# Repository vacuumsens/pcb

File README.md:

# PCB Schematic Projects

KiCad PCB design projects for VacuumSens.

## Project Structure

```
SchematicProjects/
├── libs/                    # Centralized component libraries
│   ├── easyeda2kicad.kicad_sym
│   ├── easyeda2kicad.pretty/
│   └── easyeda2kicad.3dshapes/
├── charging-circuit/V1/     # Charging circuit project
├── RS232-converter/V1/      # RS232 converter project
└── ...
```

## Importing Components from EasyEDA/LCSC

There are two methods to import components:

---

### Method 1: Command Line (easyeda2kicad)

Best for batch imports or when you know the LCSC part number.

#### Prerequisites

Install the `easyeda2kicad` Python tool:

```bash
pip install easyeda2kicad
```

#### Import a Component

Use the alias (already configured in `.zshrc`):

```bash
easyeda2kicad-import <LCSC_ID>
```

**Example:**
```bash
easyeda2kicad-import C49018
```

This downloads the symbol, footprint, and 3D model to the centralized `libs/` folder.

#### Manual Import (without alias)

```bash
easyeda2kicad --full --overwrite --output /Users/andrewyanez/Documents/KiCad/7.0/symbols/SchematicProjects/libs --lcsc_id C49018
```

---

### Method 2: KiCad Plugin (EasyEDA/LCSC Plugin)

Best for browsing and importing directly within KiCad.

#### Installation

1. In KiCad, go to **Plugin and Content Manager**
2. Search for "EasyEDA" or "LCSC"
3. Install the plugin

#### Usage

1. Open your KiCad project
2. Go to **Tools → EasyEDA Library** (or similar menu item)
3. Search for a component by name or LCSC part number
4. Click **Import** - the plugin will create:
   - `LCSC/EasyEDA.kicad_sym` (symbols)
   - `LCSC/EasyEDA.pretty/` (footprints)
   - `LCSC/EasyEDA.3dshapes/` (3D models)

**Note:** The plugin saves files locally in your project folder under `LCSC/`. This is project-specific, not centralized.

---

### After Importing (Both Methods)

1. Open your KiCad project
2. The library should be available in the schematic/PCB editor
3. Add the new symbol/footprint to your design
4. Commit changes to git:
   ```bash
   git add -A && git commit -m "Add component CXXXXX"
   git push
   ```

---

### Which Method to Use?

| Method | Pros | Cons |
|--------|------|------|
| **easyeda2kicad** (CLI) | Centralized in `libs/`, shared across projects | Requires terminal |
| **KiCad Plugin** | Visual browsing, integrated in KiCad | Project-local, can create duplicates |

**Recommendation:** Use the CLI for components you'll reuse. Use the plugin for quick project-specific imports.

## Library Configuration

Projects reference the centralized library using relative paths:

**sym-lib-table:**
```
(lib (name "easyeda2kicad")(type "KiCad")(uri "${KIPRJMOD}/../../libs/easyeda2kicad.kicad_sym"))
```

**fp-lib-table:**
```
(lib (name "easyeda2kicad")(type "KiCad")(uri "${KIPRJMOD}/../../libs/easyeda2kicad.pretty"))
```

## Finding LCSC Part Numbers

1. Go to [LCSC.com](https://www.lcsc.com) or [JLCPCB Parts](https://jlcpcb.com/parts)
2. Search for your component
3. The LCSC part number starts with "C" (e.g., C49018)

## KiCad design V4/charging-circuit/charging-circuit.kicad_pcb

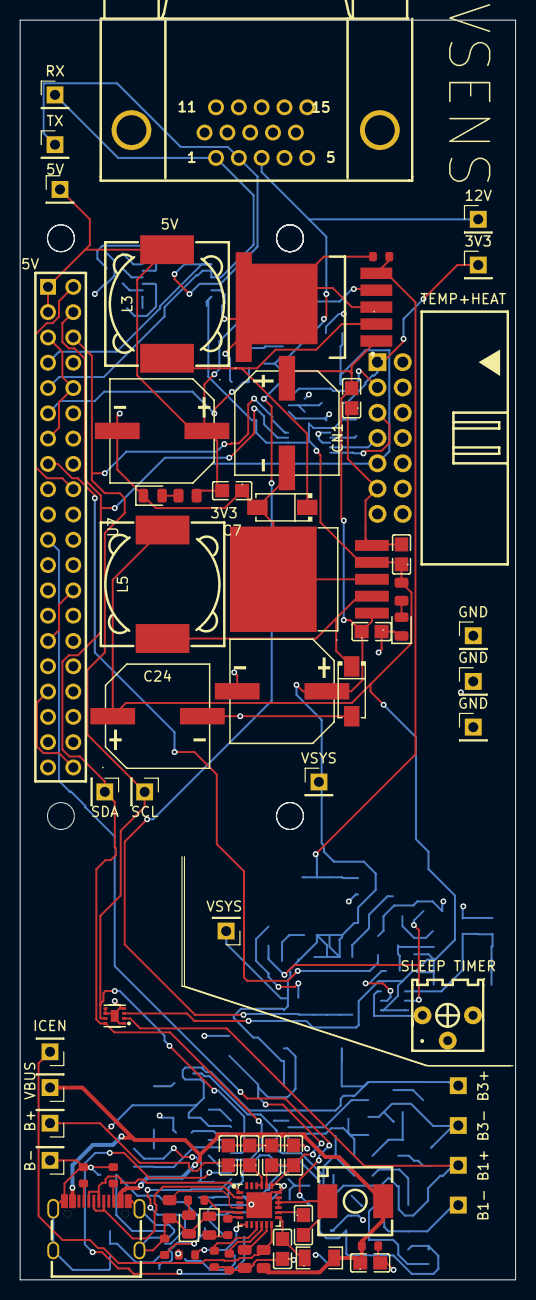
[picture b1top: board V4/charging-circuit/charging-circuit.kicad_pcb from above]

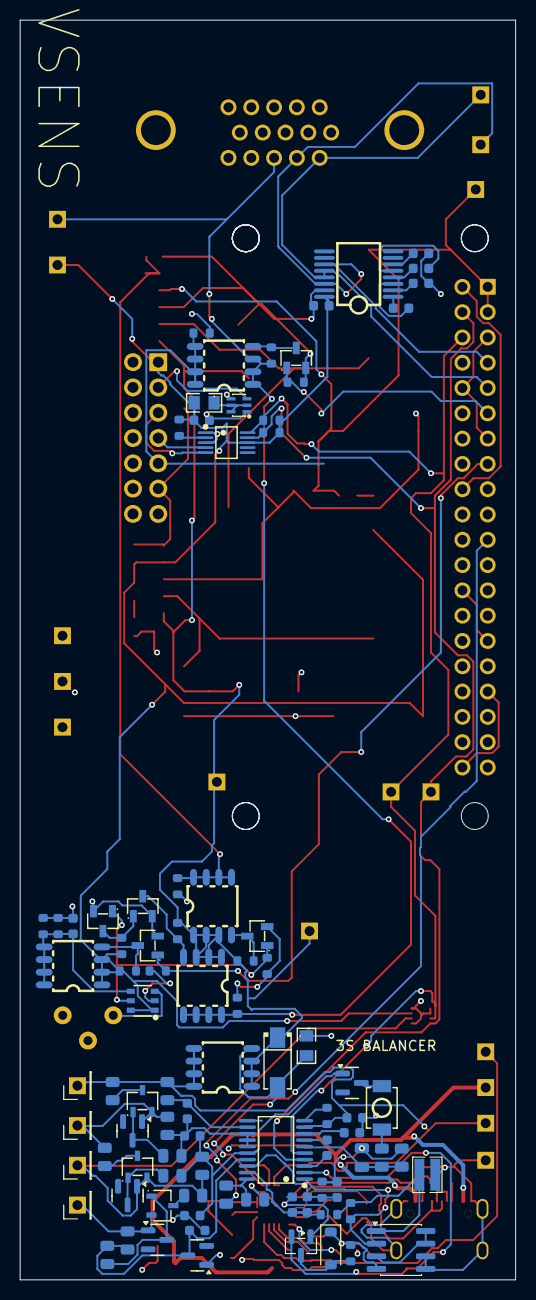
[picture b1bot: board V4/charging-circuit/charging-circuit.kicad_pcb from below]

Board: 4 copper layers, 49.8 x 126.5 mm, 153 parts (88 on the bottom side), 87 nets.

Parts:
3V3: 3V3; PinHeader_1x01_P2.54mm_Vertical
12V: 12VOUT; PinHeader_1x01_P2.54mm_Vertical
C2, C3, C6, C7, C19: 100nf; C0805
C4, C5: 22uf; C0805
C8, C10, C11, C12: 10uf; C0805
C13, C14, C15, C16, C18, C22, C29, C33, C35, C36, C65: 100nF; C_0603
C21: 330uf; CAP-SMD_BD10.0-L10.3-W10.3-FD
C23, C24, C25: 470uf; CAP-SMD_BD10.0-L10.3-W10.3-LS11.0-FD
C27: 100nF; C_0805
C38, C39: 1uF; C_0603
C40: 4.7uF; C_0603
CN1: DC3-2.54-14PAL; IDC-TH_14P-P2.54_ZHOURI_DC3-2.54-14PAL
C_sense7, C_sense8, C_sense9: 100nF; C_0603
D1, D2, D5: SS54_C22452; SMA_L4.4-W2.8-LS5.4-R-RD
D3, D6, D7, D13: BZX84C5V6; D_SOT-23
D8: Red; D_0805
D9, D10, D12: Green; D_0805
D11: 1N4148W; D_SOD-123
D14: BZX84C3V3; D_SOT-23
DSub2: DS1038-15FBNSIA74-0CC; DSUB-TH_DS1038-15FBNSIA74-0CC
GND: GND; PinHeader_1x01_P2.54mm_Vertical
GND#2, GND#3: GND; PinHeader_1x01_P2.54mm_Vertical
L1: SPM6530T-2R2M; IND-SMD_L7.1-W6.5-P5.60
L3, L5: SMDRI127-330MT; IND-SMD_L12.3-W12.3
Q1, Q2, Q3: DMN2004K-7; SOT-23-3_L3.0-W1.7-P0.95-LS2.9-BR
Q5: AO4892; SOIC-8_3.9x4.9mm_P1.27mm
Q11: BSS84; SOT-23
Q14, Q21, Q24, Q25, Q26: 2N7002; SOT-23-3_L2.9-W1.3-P1.90-LS2.4-BR
Q17, Q18, Q22, Q27, Q28: CJQ4435; SOP-8_L5.0-W4.0-P1.27-LS6.2-BL
Q23: currentmirror; SOT-363-6_L2.2-W1.3-P0.65-LS2.1-BL
R1: 0805W8F2553T5E; R0805
R2, R3: 4.7kΩ; R_0805
R4: 0.5ohm; R1206
R5: 100k; R0805
R6: 3362P-1-204; RES-ADJ-TH_3P-L7.1-W6.9-P2.50-L_3362P
R8, R13, R20: 33Ω; R_0805
R9, R10, R21, R22, R53: 1kΩ; R_0805
R11, R16, R24, R25, R26: 10kΩ; R_0805
R12: 62kΩ; R_0805
R14: 1MΩ; R_0805
R15, R52, R54: 1MΩ; R_0603
R18, R19: 51kΩ; R_0805
R31, R32, R33, R40, R44, R45: 5.1kΩ; R_0603
R37, R38, R39, R41, R43, R47, R50: 10kΩ; R_0603
R46, R48, R49, R51: 100kΩ; R_0603
RPROG8, RPROG9, RPROG10, RPROG11, RPROG12, RPROG13, RPROG14, RPROG15: 1kΩ; R_0603
RX: RX; PinHeader_1x01_P2.54mm_Vertical
R_sense5, R_sense6, R_sense7: 100Ω; R_0603
Rsense3: LTR18EZPFSR015; R0612
SW3: TS-1088R-02026; SW-SMD_L3.9-W3.0-P4.45
TP2, TP3, TP4, TP5, TP9: TestPoint; PinHeader_1x01_P2.54mm_Vertical
TP6: BAT-; PinHeader_1x01_P2.54mm_Vertical
TP7: Bat+; PinHeader_1x01_P2.54mm_Vertical
TP8: VBUS; PinHeader_1x01_P2.54mm_Vertical
TP10: VSYS; PinHeader_1x01_P2.54mm_Vertical
TP15: SDA; PinHeader_1x01_P2.54mm_Vertical
TP16: SCL; PinHeader_1x01_P2.54mm_Vertical
TP21: 5V; PinHeader_1x01_P2.54mm_Vertical
TX: TX; PinHeader_1x01_P2.54mm_Vertical
U1: IP2326; VQFN-24_L4.0-W4.0-P0.50-BL-EP2.5
U2: MAX17048G+T10; TDFN-8_L2.0-W2.0-P0.50-BL-EP1.2
U3: BQ7692003PWR; TSSOP-20_L6.5-W4.4-P0.65-LS6.4-BL
U4: LM2596SX-3.3; TO-263-5_L10.2-W8.6-P1.70-LS14.4-TL
U6: LM2596SX-5.0/NOPB; TO-263-5_L10.2-W8.9-P1.70-TL
U7: 2.54-2*20; HDR-TH_40P-P2.54-V-F-R2-C20-S2.54
U10: MAX3232CDBR; SSOP-16_L6.2-W5.3-P0.65-LS7.8-BL
U12: ADS1115IDGSR; MSOP-10_L3.0-W3.0-P0.50-LS5.0-BL
U19: TPL5110DDCT; TSOT-23-6_L2.9-W1.6-P0.95-LS2.8-BR
USBC1: TYPE-C-31-M-12; USB-C_SMD-TYPE-C-31-M-12_1
VSYS: VSYS2; PinHeader_1x01_P2.54mm_Vertical

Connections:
/3S Balancer/B1-: D7.1, Q3.2 (S), R53.1, TP2.1 (1_1)
/3S Balancer/B3-: D3.1, Q1.2 (S), R10.1, R20.1, TP4.1 (1_1)
/3S Balancer/CHG: Q11.2 (S), U3.2 (CHG)
/3S Balancer/DSG: Q5.2 (G1), R15.1, U3.1 (DSG)
/3S Balancer/PROTECT-: Q5.1 (S1), R15.2, R_sense5.2, Rsense3.1
/3S Balancer/SRN: C_sense7.2, C_sense8.1, R_sense5.1, U3.19 (SRN)
/3S Balancer/SRP: C_sense8.2, C_sense9.1, R_sense6.1, U3.18 (SRP)
/3S Balancer/TS1: C27.1, R25.1, R26.2, U3.6 (TS1)
/3S Balancer/VC0: C18.2, D14.3, R24.2, R53.2, U3.17 (VC0)
/3S Balancer/VC1: C15.2, C16.1, D13.1, R16.2, R21.2, U3.16 (VC1)
/3S Balancer/VC3: C14.2, C15.1, R10.2, R11.2, U3.13 (VC4), U3.14 (VC3), U3.15 (VC2)
/3S Balancer/VC5: C14.1, R9.2, U3.12 (VC5)
/3S IC/BAT+: C8.1, C10.1, C38.1, Q18.5 (D), Q18.6 (D), Q18.7 (D), Q18.8 (D), R8.1, R9.1, R_sense7.1, TP5.1 (1_1), TP7.1 (1_1), U1.21 (VOUT), U1.22 (VOUT), U3.9 (REGSRC)
/3S IC/DN: U1.1 (DM), USBC1.A7 (DN1), USBC1.B7 (DN2)
/3S IC/DP: U1.2 (DP), USBC1.A6 (DP1), USBC1.B6 (DP2)
/3S IC/ICEN: R19.2, TP9.1 (1_1), U1.12 (EN)
/3S IC/ICVBUS: C12.1, L1.2, R4.2, R19.1, R33.2, TP8.1 (1_1), USBC1.A4B9 (VBUS), USBC1.B4A9 (VBUS)
/5V: C7.2, C21.1, L3.2, R2.1, TP21.1 (1_1), U6.4 (FB), U7.1, U7.3
/DSUB+RS232/DSUB3.3V: 3V3.1 (1_1), C13.1, C19.1, C24.1, C33.1, CN1.1, L5.2, Q22.1 (S), Q22.2 (S), Q22.3 (S), R1.2, R3.1, R40.1, R43.2, R44.1, R45.1, R46.1, U2.3 (VDD), U4.4 (FB), U10.16 (VCC), U12.8 (VDD), U19.1 (VDD), U19.6 (EN/ONE_SHOT)
/DSUB+RS232/DSUB12V: 12V.1 (1_1), DSub2.3, Q17.1 (S), Q17.2 (S), Q17.3 (S), Q28.5 (D), Q28.6 (D), Q28.7 (D), Q28.8 (D), R39.2, R49.2
/FUELGAUGE/FUELBAT: D6.1, Q2.2 (S), R13.1, R21.1, TP3.1 (1_1), U2.2 (CELL)
/GND: C3.2, C4.1, C5.1, C6.1, C7.1, C8.2, C10.2, C11.1, C12.2, C13.2, C16.2, C18.1, C19.2, C21.2, C23.2, C24.2, C25.2, C27.2, C29.2, C33.2, C35.2, C38.2, C40.2, C65.2, CN1.11, C_sense7.1, C_sense9.2, D2.1 (A), D5.1 (A), D8.1, D9.1, D10.1, D12.1, D14.1, DSub2.4, GND.1 (1_1), GND#2.1 (1_1), GND#3.1 (1_1), Q5.5 (D2), Q5.6 (D2), Q11.1 (G), Q14.2 (S), Q21.2 (S), Q23.1 (E), Q23.4 (E), Q24.2 (S), Q25.2 (S), Q26.2 (S), R5.1, R6.2, R12.1, R14.2, R18.1, R25.2, R31.1, R32.1, R33.1, R37.2, R38.2, R41.1, R49.1, R50.2, R51.2, R54.2, RPROG8.2, RPROG9.2, RPROG10.2, RPROG11.2, RPROG14.2, RPROG15.2, R_sense6.2, Rsense3.2, TP6.1 (1_1), U1.18 (PGND), U1.25 (EP), U2.1 (CTG), U2.4 (GND), U2.5 (~ALRT), U2.6 (QSTRT), U2.9 (EP), U4.3 (GND), U4.5 (~ON/OFF), U4.6 (GND), U6.3 (GND), U6.6 (GND), U7.5, U7.10, U7.13, U7.19, U7.26, U7.29, U7.33, U7.40, U10.15 (GND), U12.1 (ADDR), U12.3 (GND), U19.2 (GND), USBC1.1 (EH), USBC1.2 (EH), USBC1.3 (EH), USBC1.4 (EH), USBC1.A1B12 (GND), USBC1.B1A12 (GND)
/GPIO2/SDA1: R44.2, TP15.1 (1_1), U2.8 (SDA), U3.4 (SDA), U7.4, U12.9 (SDA)
/GPIO3/SCL1: R45.2, TP16.1 (1_1), U2.7 (SCL), U3.5 (SCL), U7.6, U12.10 (SCL)
/GPIO14/TXD0: DSub2.2, TX.1 (1_1), U7.7, U10.11 (DIN1), U10.14 (DOUT1)
/GPIO15/RXD0: DSub2.1, RX.1 (1_1), U7.9, U10.12 (ROUT1), U10.13 (RIN1)
/GPIO18/PCM.CLK: Q14.1 (G), R50.1, U7.11
/GPIO23: Q21.1 (G), R41.2, U7.15
/GPIO25: R22.1, U7.21
/LM2596 3V3 BUCK/LM2596_VIN: C3.1, C6.2, C23.1, C25.1, D1.2 (K), Q18.1 (S), Q18.2 (S), Q18.3 (S), Q27.1 (S), Q27.2 (S), Q27.3 (S), Q28.1 (S), Q28.2 (S), Q28.3 (S), R47.2, R48.2, TP10.1 (1_1), U4.1 (VIN), U6.1 (VIN), VSYS.1 (1_1)
/LM2596 3V3 BUCK/SW: D5.2 (K), L5.1, U4.2 (OUT)
/LM2596 5V Buck/SW: D2.2 (K), L3.1, U6.2 (OUTPUT)
/Load Sharing/VSYS: C4.2, C5.2, D1.1 (A), Q18.4 (G), R5.2, U1.19 (VSYS), U1.20 (VSYS)
/SLEEPMOSFET/5EN: Q27.5 (D), Q27.6 (D), Q27.7 (D), Q27.8 (D), R51.1, RPROG10.1, U6.5 (~ON/OFF)
/SLEEPMOSFET/SLPDRV: Q24.1 (G), Q25.1 (G), R38.1, U19.5 (DRV)
/SLEEPMOSFET/SLPSIG: C65.1, Q22.5 (D), Q22.6 (D), Q22.7 (D), Q22.8 (D), R37.1, RPROG9.1, U19.4 (DONE)
/TEMP+HEATER/A0: CN1.7, U12.4 (AIN0)
/TEMP+HEATER/A1: CN1.5, U12.5 (AIN1)
/TEMP+HEATER/DIODEI-: CN1.3, Q23.3 (C)
/TEMP+HEATER/HEATER+: CN1.9, Q17.5 (D), Q17.6 (D), Q17.7 (D), Q17.8 (D), RPROG8.1
/TEMP+HEATER/base: Q23.2 (B), Q23.5 (B), Q23.6 (C), R1.1
/raspi3.3V: U7.2, U7.18
unnamed: C2.2, L1.1, U1.15 (LX), U1.16 (LX), U1.17 (LX)
unnamed: D8.2, RPROG13.2
unnamed: D9.2, RPROG12.2
unnamed: D10.2, R2.2
unnamed: D11.2 (A), Q11.3 (D), R52.1
unnamed: D11.1 (K), Q5.4 (G2), R52.2, R54.1
unnamed: D12.2, R3.2
unnamed: D13.3, SW3.1
unnamed: Q1.3 (D), R8.2
unnamed: D3.3, Q1.1 (G), R11.1
unnamed: Q2.3 (D), R20.2
unnamed: D6.3, Q2.1 (G), R16.1
unnamed: Q3.3 (D), R13.2
unnamed: D7.3, Q3.1 (G), R24.1
unnamed: Q5.3 (S2), Q5.7 (D1), Q5.8 (D1)
unnamed: Q14.3 (D), Q17.4 (G), R39.1
unnamed: Q21.3 (D), Q22.4 (G), R43.1
unnamed: Q24.3 (D), Q26.1 (G), R46.2
unnamed: Q25.3 (D), Q27.4 (G), R47.1
unnamed: Q26.3 (D), Q28.4 (G), R48.1
unnamed: R26.1, SW3.2
unnamed: RPROG13.1, U1.5 (BAT_STAT)
unnamed: C2.1, U1.14 (BST)
unnamed: RPROG11.1, U1.10 (CON_SEL)
unnamed: R12.2, U1.11 (ISET)
unnamed: RPROG12.1, U1.6 (LED)
unnamed: R18.2, U1.4 (NTC)
unnamed: RPROG14.1, U1.7 (TIME_SET)
unnamed: C11.2, R4.1, U1.13 (VIN)
unnamed: RPROG15.1, U1.9 (VIN_OVSET)
unnamed: R14.1, R22.2, U3.20 (ALERT)
unnamed: R_sense7.2, U3.10 (BAT)
unnamed: C39.1, U3.7 (CAP1)
unnamed: C40.1, U3.8 (REGOUT)
unnamed: C39.2, U3.3 (VSS)
unnamed: C22.1, U10.1 (C1+)
unnamed: C22.2, U10.3 (C1-)
unnamed: C36.1, U10.4 (C2+)
unnamed: C36.2, U10.5 (C2-)
unnamed: C29.1, U10.2 (V+)
unnamed: C35.1, U10.6 (V-)
unnamed: R40.2, U12.2 (ALERT/RDY)
unnamed: R6.3, U19.3 (DELAY/M_DRV)
unnamed: R32.2, USBC1.A5 (CC1)
unnamed: R31.2, USBC1.B5 (CC2)

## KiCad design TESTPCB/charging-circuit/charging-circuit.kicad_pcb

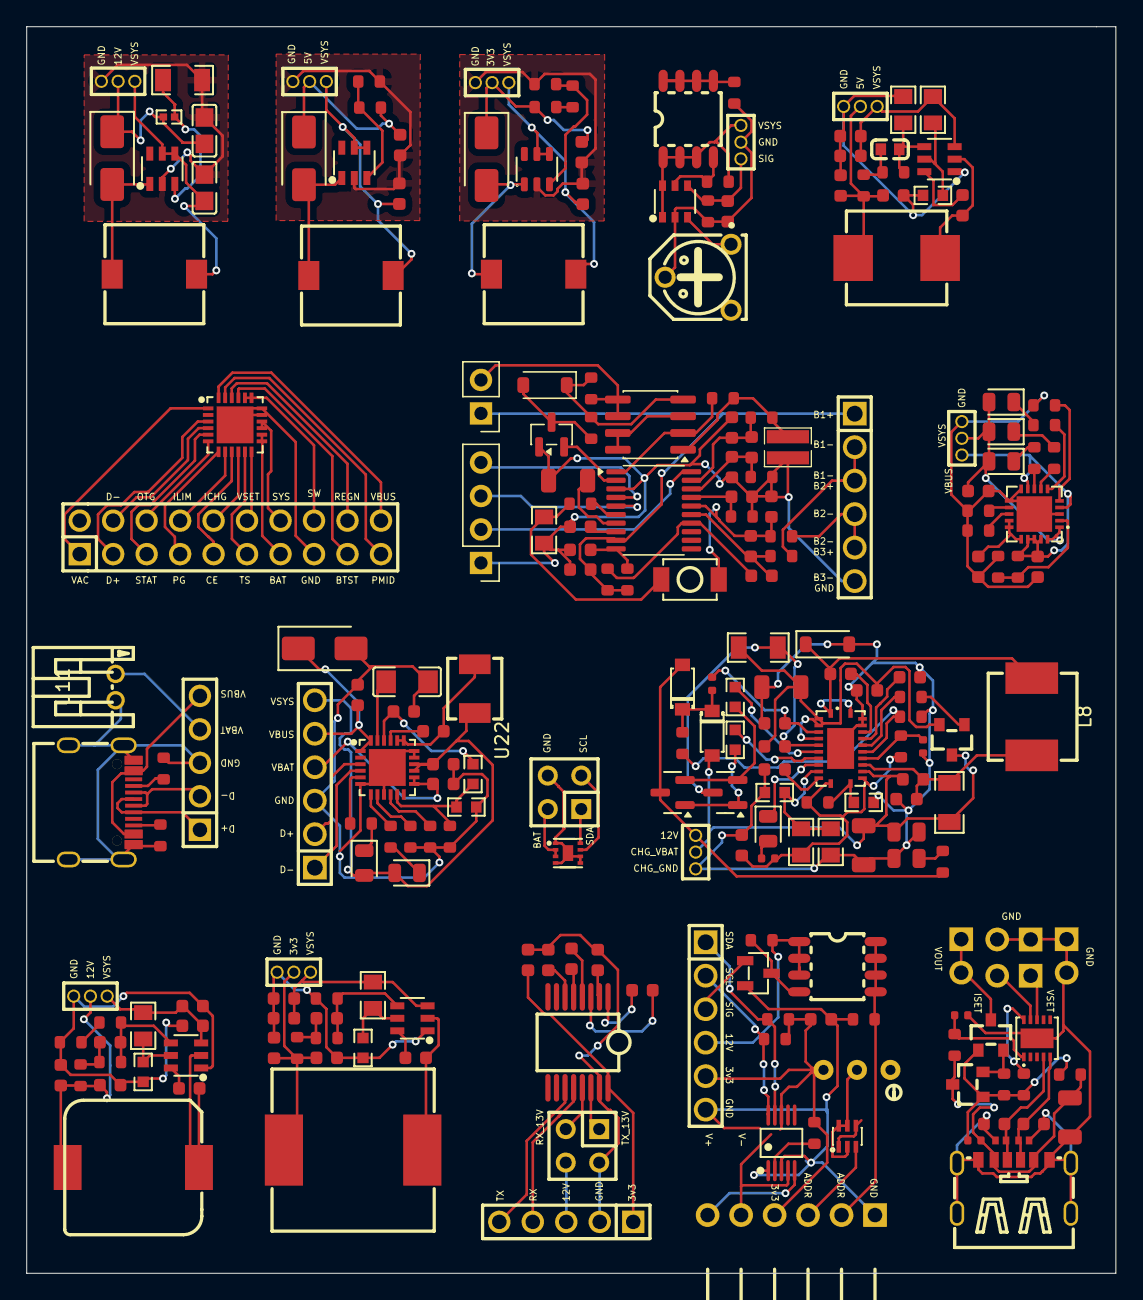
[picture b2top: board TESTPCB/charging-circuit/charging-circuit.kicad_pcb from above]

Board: 2 copper layers, 82.6 x 94.6 mm, 232 parts (0 on the bottom side), 196 nets.

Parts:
C1, C2: 22uf; C0805
C3, C5, C6, C12, C17, C18, C19, C20, C21, C32, C33, C34, C38, C44, C45, C54, C57, C61: 100nF; C_0603
C4, C7, C10, C11, C35, C36, C40, C41, C46, C47: 22uF; C_0603
C8, C14, C22, C29, C37, C43, C50: 10uF; C_0603
C9, C31, C42, C53, C55, C70, C71: 1uF; C_0603
C13: 22uf; C1206
C15, C23, C51, C52: 4.7uF; C_0603
C16, C56: 47nF; C_0603
C24, C25: 330pF; C_0603
C26, C28: 1uF; C_0402
C27, C58, C72: 10uF; C_1206
C30: 1uF; C_1206
C39: 47pF; C_0603
C48: 75pf; C0603
C49: 100pF; C_0603
C59: 22uF; C_0805
C_sense1, C_sense2, C_sense3: 100nF; C_0603
Cc0, Cc1: 1uF; C_0603
Cin1: 2.2uF; C_0805
D1: 1N4148W; D_SOD-123
D2, D11: H5VU10U; D_DFN1006-2L
D3, D9, D13: Green; D_0805
D4, D5, D6: SS34; D_SMA
D7, D8: Red; D_0805
D10: Yellow; D_0805
D12, D100: MBR0530; SOD-123_L2.8-W1.8-LS3.7-RD
D14: SS14; D_SMA
D19: B0530W; D_SOD-123
H2, H11: 77311-462K05LF; HDR-TH_5P-P2.54-V-M
H3, H4, H9: Header-Male-2.54_1x6; HDR-TH_6P-P2.54-V-M-1
H5, H6, H7, H8: 68000-102HLF; HDR-TH_2P-P2.54-V-M-1
J1: 2.54-1*6PHeader-RA; HDR-TH_6P-P2.54-H-M-W10.0
J2: USB_C_Receptacle_PowerOnly_6P; TYPE-C-SMD_TYPE-C-6P
J10: Conn_01x02; PinHeader_1x02_P2.54mm_Vertical
J11: Conn_01x04; PinHeader_1x04_P2.54mm_Vertical
L1, L2, L3: 22uH; IND-SMD_L7.5-W7.5
L5: 10uh; IND-SMD_L7.5-W6.6
L6: 6.8uh; IND-SMD_L12.3-W12.3_SMDRI127
L7: 15uh; IND-SMD_L10.4-W10.3
L8: 2.2uH; IND-SMD_L6.7-W6.6
P1, P2: Header-Male-2.54_2x2; HDR-TH_4P-P2.54-V-M-R2-C2-S2.54-1
P3, P4, P5, P6, P7, P8, P9, P10, P11: 1.27mm/1*3p; HDR-TH_3P-P1.27-V-M-1
Q1: 2N7002; SOT-23-3_L2.9-W1.3-P1.90-LS2.4-BR
Q2, Q8: CJQ4435; SOP-8_L5.0-W4.0-P1.27-LS6.2-BL
Q3: currentmirror; SOT-363-6_L2.2-W1.3-P0.65-LS2.1-BL
Q4: BSS84; SOT-23
Q5: AO4892; SOIC-8_3.9x4.9mm_P1.27mm
Q6, Q7, Q11: AO3401A; SOT-23_L2.9-W1.3-P1.90-LS2.4-BR
Q9, Q10: AO3400A; Q_SOT-23
R1: 11.3kohm; R1206
R2: 215kohm; R0402
R3, R46: 3kΩ; R_0603
R4: 10Ω; R_0402
R5: 5.23k; R0805
R6, R38, R45, R50, R61, R76: 100kΩ; R_0603
R7: 32.4k; R0603
R8, R9, R14, R16, R29, R39: 10kΩ; R_0603
R10, R52: 22kΩ; R_0603
R11, R15, R26, R60: 1MΩ; R_0603
R12, R13, R21, R30, R31, R35: 5.1kΩ; R_0603
R17, R20, R24, R53: 2.2kΩ; R_0603
R18: 6.8kΩ; R_0603
R19: 2kΩ; R_0603
R22: 240Ω; R_0603
R25: 150Ω; R_0603
R27: 5.23kohm; R0603
R28: 30.1kohm; R0603
R32: 100Ω; R_0603
R33: 10Ω; R_0603
R34: 330kΩ; R_0603
R36: 12kΩ; R_0603
R37, R44, R49, R77: 49.9kΩ; R_0603
R40, R42, R47: 511k; R0805
R41, R43, R48: 105k; R0603
R51: 13.3k; R0805
R54: RM065-204(200K); RES-ADJ-TH_3P-L7.3-W6.4-P5.00-R
R55: 3296W-1-504LF; RES-ADJ-TH_3296W
R56, R57, R58: 470Ω; R_0603
R59: 110kΩ; R_0603
R62: 30.1k; R0603
R63, R75: 4.02k; R0603
R64: 1.5kΩ; R_0402
R65: 1kΩ; R_0603
R66: 33kΩ; R_0402
RPROG1, RPROG2, RPROG5: 1kΩ; R_0603
RPROG3: 10kΩ; R_0603
R_AC1, R_AC2: 10m; R1206
R_sense1, R_sense2: 100Ω; R_0603
Rc0, Rc1, Rc2, Rc3: 100Ω; R_0603
Rin1: 2Ω; R_0603
Rsense1: LTR18EZPFSR015; R0612
SW1: TS-1088R-02026; SW-SMD_L3.9-W3.0-P4.45
U1: MAX17048G+T10; TDFN-8_L2.0-W2.0-P0.50-BL-EP1.2
U2, U3, U6: MT3608; SOT-23-6_L2.9-W1.6-P0.95-LS2.8-BL
U4: TPL5110DDCT; TSOT-23-6_L2.9-W1.6-P0.95-LS2.8-BR
U5, U10: BQ25606RGER; VQFN-24_L4.0-W4.0-P0.50-TL-EP2.8
U7: Z-21320110021001; HDR-TH_20P-P2.54-V-M-R2-C10-S2.54
U8: MAX3232CDBR; SSOP-16_L6.2-W5.3-P0.65-LS7.8-BL
U9: ADS1115IDGSR; MSOP-10_L3.0-W3.0-P0.50-LS5.0-BL
U11: Battery Input; CONN-TH_S2B-PH-K-S-GW
U12: BQ24170RGYR; VQFN-24_L5.5-W3.5-P0.50-BL-EP-2
U13, U19, U20: TPS54302DDCR_C311983; SOT-23-6_L2.9-W1.6-P0.95-LS2.8-BL
U14, U16: NTC10K/0805/F; R0805
U15: BQ76920PW; TSSOP-20_4.4x6.5mm_P0.65mm
U17: HUSB238_002DD; DFN-10_L3.0-W3.0-P0.50-BL-EP2.5
U21: MCP73871; QFN-20_L4.0-W4.0-P0.5-BL-EP
U22: SRP4020TA-1R0M; IND-SMD_L4.5-W4.1_SRP4020TA
USBC1: TYPE-C-31-M-12; USB-C_SMD-TYPE-C-31-M-12_1

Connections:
1D+: H3.2, U10.3 (D+)
1D-: H3.1, U10.4 (D-)
2D+: U5.3 (D+), U7.3
2D-: U5.4 (D-), U7.4
3V3BGND: C29.2, C32.2, C40.2, C41.2, P4.3, R43.1, R52.2, U13.1 (GND)
3V3BOOT: C33.2, L6.1, U13.2 (SW)
3V3BVOUT: C40.1, C41.1, L6.2, P4.2, R44.1
3V3BVSYS: C29.1, C32.1, P4.1, R42.2, U13.3 (VIN)
3V3FB: C39.2, R45.2, R52.1, U13.4 (FB)
3V3GND: C10.2, C11.1, P7.3, R19.2, U6.2 (GND)
3V3VOUT: C11.2, D6.1, P7.2, R18.1
3V3VSYS: C10.1, L3.1, P7.1, U6.4 (EN), U6.5 (IN)
5BGND: C43.2, C44.2, C46.2, C47.2, P9.3, R48.1, R51.2, U20.1 (GND)
5BOOT: C45.2, L5.1, U20.2 (SW)
5BVOUT: C46.1, C47.1, L5.2, P9.2, R49.1
5BVSYS: C43.1, C44.1, P9.1, R47.2, U20.3 (VIN)
5FB: C48.1, R50.2, R51.1, U20.4 (FB)
5GND: C4.1, C7.2, P6.3, R3.2, U2.2 (GND)
5VOUT: C4.2, D5.1, P6.2, R10.1
5VSYS: C7.1, L1.1, P6.1, U2.4 (EN), U2.5 (IN)
12BGND: C35.2, C36.2, C37.2, C38.2, P8.3, R41.1, R46.1, U19.1 (GND)
12BOOT: C34.2, L7.1, U19.2 (SW)
12BVOUT: C35.1, C36.1, L7.2, P8.2, R37.1
12BVSYS: C37.1, C38.1, P8.1, R40.2, U19.3 (VIN)
12FB: C49.2, R38.2, R53.1, U19.4 (FB)
12GND: C1.1, C2.1, P5.3, R1.1, U3.2 (GND)
12VOUT: C1.2, D4.1, P5.2, R2.1
12VSYS: C2.2, L2.1, P5.1, U3.4 (EN), U3.5 (IN)
12V_Adapter: D12.2 (A), P11.1, Q9.3 (D), Rin1.1
A0: J1.5, U9.4 (AIN0)
A1: J1.6, U9.5 (AIN1)
ALERT-2-RASPI: J11.2, U15.20 (ALERT)
BAT2: U5.13 (BAT), U5.14 (BAT), U7.13
BAT_1 (+): C31.2, H9.1, J10.1, R32.1, Rc3.2, U15.9 (REGSRC)
BAT_1 (-): H9.2, H9.3, Rc2.2
BAT_2 (-): H9.4, H9.5, Rc1.2
BAT_3 (-): C8.1, C23.2, C30.1, C31.1, C_sense1.1, C_sense3.2, Cc0.2, Cc1.2, H9.6, J11.1, Q4.1 (G), R_sense2.2, Rc0.2, Rsense1.2, U14.2, U15.3 (VSS)
BTST: U5.21 (BTST), U7.17
CC1: C25.1, D2.1, J2.A5 (CC1), U17.4 (CC1)
CC2: C24.1, D11.1, J2.B5 (CC2), U17.5 (CC2)
CE2: U5.9 (~CE), U7.9
CHG_GND: C6.2, C42.2, C53.2, C55.2, C57.2, C58.2, C59.2, C61.1, C72.2, Cin1.2, D19.2, P11.3, R7.1, R61.2, R62.2, R66.2, U12.22 (PGND), U12.23 (PGND), U12.25 (EP), U16.2
CHG_VBAT: C54.1, C58.1, C59.1, D100.2 (A), P11.2, Q11.3 (D), R_AC1.2, U12.15 (SRN)
D+: H2.1, USBC1.A6 (DP1), USBC1.B6 (DP2)
D-: H2.2, USBC1.A7 (DN1), USBC1.B7 (DN2)
DSUB3.3V: C21.1, H11.1, U8.16 (VCC)
DSUB12V: H11.3, P1.4
DSUBGND: C17.2, C18.2, C21.2, H11.2, P1.2, U8.15 (GND)
FUELBAT: P2.2, U1.2 (CELL), U1.3 (VDD)
FUELGND: P2.4, U1.1 (CTG), U1.4 (GND), U1.5 (~ALRT), U1.6 (QSTRT), U1.9 (EP)
FUELSCL: P2.3, U1.7 (SCL)
FUELSDA: P2.1, U1.8 (SDA)
GND1: C9.1, C13.2, C14.1, C15.2, C22.1, D14.2, H3.3, R22.1, R25.1, R28.2, R29.2, U10.6 (OTG), U10.9 (~CE), U10.17 (GND), U10.18 (GND), U10.25 (EP)
GND2: U5.17 (GND), U5.18 (GND), U5.25 (EP), U7.15
ICHG2: U5.10 (ICHG), U7.10
ILIM2: U5.8 (ILIM), U7.8
ISET: H5.2, U17.9 (ISET)
unnamed: C16.2, U10.19 (SW), U10.20 (SW), U22.1
unnamed: C39.1, R44.2, R45.1
unnamed: C48.2, R49.2, R50.1
unnamed: C49.1, R37.2, R38.1
unnamed: C56.1, D19.1, L8.1, U12.1 (SW), U12.24 (SW)
unnamed: Cin1.1, Rin1.2
unnamed: D1.2 (A), Q4.3 (D), R15.1
unnamed: D1.1 (K), Q5.4 (G2), R15.2, R26.1
unnamed: D3.1, R58.1
unnamed: D7.1, R57.1
unnamed: D8.1, R17.1
unnamed: D9.1, R24.1
unnamed: D10.1, R56.1
unnamed: D13.2, R64.2
unnamed: D12.1 (C), D100.1 (C), R4.1, R60.1
unnamed: J1.2, Q2.5 (D), Q2.6 (D), Q2.7 (D), Q2.8 (D), RPROG5.1
unnamed: J1.3, Q3.3 (C)
unnamed: Q1.3 (D), Q2.4 (G), R14.1
unnamed: Q4.2 (S), U15.2 (CHG)
unnamed: Q5.2 (G1), R11.1, U15.1 (DSG)
unnamed: Q5.3 (S2), Q5.7 (D1), Q5.8 (D1)
unnamed: C26.1, Q6.1 (G), Q7.1 (G), R35.2, R36.2, R77.2
unnamed: Q6.2 (S), Q7.2 (S), R77.1
unnamed: C26.2, C27.1, J2.A9 (VBUS), J2.B9 (VBUS), Q7.3 (D), R33.1, R36.1
unnamed: Q8.5 (D), Q8.6 (D), Q8.7 (D), Q8.8 (D), RPROG1.1
unnamed: Q8.4 (G), R9.1, U4.5 (DRV)
unnamed: C5.1, Q10.3 (D), R_AC2.1, U12.6 (ACP)
unnamed: Q9.1 (G), Q10.1 (G), R63.1
unnamed: Q9.2 (S), Q10.2 (S), R75.1
unnamed: Q11.1 (G), R65.2
unnamed: C5.2, C6.1, C72.1, Q11.2 (S), R_AC2.2, U12.2 (PVCC), U12.3 (PVCC), U12.5 (ACN)
unnamed: R16.1, SW1.2, U14.1
unnamed: R18.2, R20.1
unnamed: R46.2, R53.2
unnamed: R3.1, R10.2, U2.3 (FB)
unnamed: D5.2, L1.2, U2.1 (SW)
unnamed: R1.2, R2.2, U3.3 (FB)
unnamed: D4.2, L2.2, U3.1 (SW)
unnamed: R54.1, U4.3 (DELAY/M_DRV)
unnamed: R19.1, R20.2, U6.3 (FB)
unnamed: D6.2, L3.2, U6.1 (SW)
unnamed: C20.1, U8.1 (C1+)
unnamed: C20.2, U8.3 (C1-)
unnamed: C19.1, U8.4 (C2+)
unnamed: C19.2, U8.5 (C2-)
unnamed: C18.1, U8.2 (V+)
unnamed: C17.1, U8.6 (V-)
unnamed: R13.2, U9.2 (ALERT/RDY)
unnamed: C16.1, U10.21 (BTST)
unnamed: R22.2, U10.10 (ICHG)
unnamed: R25.2, U10.8 (ILIM)
unnamed: C13.1, U10.23 (PMID)
unnamed: R17.2, U10.5 (STAT)
unnamed: R27.2, R28.1, R29.1, U10.11 (TS)
unnamed: R24.2, U10.7 (~PG)
unnamed: R63.2, U12.8 (ACDRV)
unnamed: R6.2, R66.1, U12.17 (ACSET)
unnamed: C53.1, R4.2, U12.4 (AVCC)
unnamed: C56.2, U12.21 (BTST)
unnamed: R75.2, U12.7 (CMSRC)
unnamed: R7.2, R76.2, U12.13 (ISET)
unnamed: R60.2, R61.1, U12.18 (OVPSET)
unnamed: C55.1, U12.20 (REGN)
unnamed: C54.2, C57.1, L8.2, R_AC1.1, U12.16 (SRP)
unnamed: D13.1, U12.9 (STAT)
unnamed: R5.2, R62.1, U12.10 (TS), U16.1
unnamed: C61.2, U12.11 (TTC)
unnamed: R65.1, U12.19 (~BATDRV)
unnamed: C33.1, U13.6 (BOOT)
unnamed: R42.1, R43.2, U13.5 (EN)
unnamed: C8.2, R32.2, U15.10 (BAT)
unnamed: C30.2, U15.7 (CAP1)
unnamed: C_sense1.2, C_sense2.1, R_sense1.1, U15.19 (SRN)
unnamed: C_sense2.2, C_sense3.1, R_sense2.1, U15.18 (SRP)
unnamed: R16.2, U15.6 (TS1)
unnamed: Cc0.1, Rc0.1, U15.17 (VC0)
unnamed: C70.2, C71.1, Rc2.1, U15.15 (VC2)
unnamed: C70.1, Rc3.1, U15.14 (VC3)
unnamed: R35.1, U17.10 (GATE)
unnamed: C28.1, R33.2, U17.1 (VIN)
unnamed: C34.1, U19.6 (BOOT)
unnamed: R40.1, R41.2, U19.5 (EN)
unnamed: C45.1, U20.6 (BOOT)
unnamed: R47.1, R48.2, U20.5 (EN)
unnamed: RPROG2.2, U21.13 (PROG1)
unnamed: RPROG3.1, U21.12 (PROG3)
unnamed: R57.2, U21.8 (STAT1/~LBO)
unnamed: R58.2, U21.7 (STAT2)
unnamed: R39.1, U21.5 (THERM)
unnamed: R34.2, R59.1, U21.2 (VPCC)
unnamed: R56.2, U21.6 (~PG)
unnamed: R31.1, USBC1.A5 (CC1)
unnamed: R30.1, USBC1.B5 (CC2)
OTG2: U5.6 (OTG), U7.6
PACK-: J10.2, Q5.5 (D2), Q5.6 (D2), R26.2
PDGND: C24.2, C25.2, C27.2, C28.2, D2.2, D11.2, H6.1, H6.2, H7.1, H7.2, J2.A12 (GND), J2.B12 (GND), J2.S1 (SHIELD), U17.11 (GND)
PDVOUT: H8.1, H8.2, Q6.3 (D)
PG2: U5.7 (~PG), U7.7
PMID2: U5.23 (PMID), U7.19
PROTECT-: Q5.1 (S1), R11.2, R_sense1.2, Rsense1.1
PWMSIG: H4.3, Q1.1 (G)
REGN1: C15.1, R27.1, U10.22 (REGN)
REGN2: U5.22 (REGN), U7.18
RX: H11.4, U8.12 (ROUT1)
SCL-2-RASPI: J11.3, U15.5 (SCL)
SDA-2-RASPI: J11.4, U15.4 (SDA)
SLEEPGND: C3.2, P3.2, R8.2, R54.2, RPROG1.2, U4.2 (GND)
SLEEPSIG: C3.1, P3.3, R8.1, U4.4 (DONE)
SLEEPVSYS: P3.1, Q8.1 (S), Q8.2 (S), Q8.3 (S), R9.2, U4.1 (VDD), U4.6 (EN/ONE_SHOT)
STAT2: U5.5 (STAT), U7.5
SW2: U5.19 (SW), U5.20 (SW), U7.16
SYS2: U5.15 (SYS), U5.16 (SYS), U7.14
TEMP12V: H4.4, Q2.1 (S), Q2.2 (S), Q2.3 (S), R14.2
TEMPGND: C12.2, H4.6, J1.1, Q1.2 (S), Q3.1 (E), Q3.4 (E), RPROG5.2, U9.1 (ADDR), U9.3 (GND)
TEMPSCL: H4.2, R12.2, U9.10 (SCL)
TEMPSDA: H4.1, R21.2, U9.9 (SDA)
TS2: U5.11 (TS), U7.11
TX: H11.5, U8.11 (DIN1)
Temp3.3V: C12.1, H4.5, J1.4, R12.1, R13.1, R21.1, R55.3, U9.8 (VDD)
UART_RX_13V: P1.3, U8.13 (RIN1)
UART_TX_13V: P1.1, U8.14 (DOUT1)
USBGND: H2.3, R30.2, R31.2, U11.2, USBC1.1 (EH), USBC1.2 (EH), USBC1.3 (EH), USBC1.4 (EH), USBC1.A1B12 (GND), USBC1.B1A12 (GND)
V1GND: C50.1, C51.1, C52.1, P10.3, R39.2, R59.2, RPROG2.1, RPROG3.2, U21.3 (SEL), U21.10 (V_{SS}), U21.11 (V_{SS}), U21.21 (V_{SS})
V1VBAT: C52.2, U21.14 (V_{BAT}), U21.15 (V_{BAT}), U21.16 (V_{BAT_SENSE})
V1VBUS: C50.2, P10.1, R34.1, U21.4 (PROG2), U21.9 (~TE), U21.17 (CE), U21.18 (IN), U21.19 (IN)
V1VSYS: C51.2, D3.2, D7.2, D10.2, P10.2, U21.1 (OUT), U21.20 (OUT)
VAC2: U5.1 (VAC), U7.1
VBAT: H2.4, U11.1
VBAT1: C14.2, H3.4, U10.13 (BAT), U10.14 (BAT)
VBUS: H2.5, USBC1.A4B9 (VBUS), USBC1.B4A9 (VBUS)
VBUS1: C9.2, D14.1, H3.5, U10.1 (VAC), U10.24 (VBUS)
VBUS2: U5.24 (VBUS), U7.20
VC1: C71.2, Cc1.1, Rc1.1, SW1.1, U15.16 (VC1)
VCC: C23.1, U15.8 (REGOUT)
VREF: C42.1, R5.1, R6.1, R64.1, R76.1, U12.12 (VREF), U12.14 (CELL/FB)
VSET: H5.1, U17.8 (VSET)
VSET2: U5.12 (VSET), U7.12
VSYS1: C22.2, D8.2, D9.2, H3.6, U10.15 (SYS), U10.16 (SYS), U22.2
base: Q3.2 (B), Q3.5 (B), Q3.6 (C), R55.2

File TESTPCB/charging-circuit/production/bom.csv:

Designator,Footprint,Quantity,Value,LCSC Part #
"C1, C2",C0805,2,22uf,C45783
"C10, C11, C35, C36, C4, C40, C41, C46, C47, C7",C_0603,10,22uF,C59461
"C12, C17, C18, C19, C20, C21, C3, C32, C33, C34, C38, C44, C45, C5, C54, C57, C6, C61, C_SENSE1, C_SENSE2, C_SENSE3",C_0603,21,100nF,C14663
C13,C1206,1,22uf,C1859
"C14, C22, C29, C37, C43, C50, C8",C_0603,7,10uF,C19702
"C15, C23, C51, C52",C_0603,4,4.7uF,C19666
"C16, C56",C_0603,2,47nF,C1622
"C24, C25",C_0603,2,330pF,C1664
"C26, C28",C_0402,2,1uF,C52923
"C27, C58, C72",C_1206,3,10uF,C13585
C30,C_1206,1,1uF,C1848
"C31, C42, C53, C55, C70, C71, C9, CC0, CC1",C_0603,9,1uF,C15849
C39,C_0603,1,47pF,C1671
C48,C0603,1,75pf,C1681
C49,C_0603,1,100pF,C14858
C59,C_0805,1,22uF,C45783
CIN1,C_0805,1,2.2uF,C377773
D1,D_SOD-123,1,1N4148W,
D10,D_0805,1,Yellow,C2296
"D100, D12",SOD-123_L2.8-W1.8-LS3.7-RD,2,MBR0530,C77336
"D11, D2",D_DFN1006-2L,2,H5VU10U,C22395519
"D13, D3, D9",D_0805,3,Green,C2297
D14,D_SMA,1,SS14,C2480
D19,D_SOD-123,1,B0530W,C7502708
"D4, D5, D6",D_SMA,3,SS34,C8678
"D7, D8",D_0805,2,Red,C84256
"H11, H2",HDR-TH_5P-P2.54-V-M,2,77311-462K05LF,C180219
"H3, H4, H9",HDR-TH_6P-P2.54-V-M-1,3,Header-Male-2.54_1x6,C37208
"H5, H6, H7, H8",HDR-TH_2P-P2.54-V-M-1,4,68000-102HLF,C168673
J1,HDR-TH_6P-P2.54-H-M-W10.0,1,2.54-1*6PHeader-RA,C56816
J10,PinHeader_1x02_P2.54mm_Vertical,1,Conn_01x02,C5360898
J11,PinHeader_1x04_P2.54mm_Vertical,1,Conn_01x04,C5116483
J2,TYPE-C-SMD_TYPE-C-6P,1,USB_C_Receptacle_PowerOnly_6P,C283540
"L1, L2, L3",IND-SMD_L7.5-W7.5,3,22uH,C19268629
L5,IND-SMD_L7.5-W6.6,1,10uh,C3002650
L6,IND-SMD_L12.3-W12.3_SMDRI127,1,6.8uh,C10149
L7,IND-SMD_L10.4-W10.3,1,15uh,C16113
L8,IND-SMD_L6.7-W6.6,1,2.2uH,C1329579
"P1, P2",HDR-TH_4P-P2.54-V-M-R2-C2-S2.54-1,2,Header-Male-2.54_2x2,C66690
"P10, P11, P3, P4, P5, P6, P7, P8, P9",HDR-TH_3P-P1.27-V-M-1,9,1.27mm/1*3p,C24980
Q1,SOT-23-3_L2.9-W1.3-P1.90-LS2.4-BR,1,2N7002,C8545
"Q10, Q9",Q_SOT-23,2,AO3400A,C20917
"Q11, Q6, Q7",SOT-23_L2.9-W1.3-P1.90-LS2.4-BR,3,AO3401A,C15127
"Q2, Q8",SOP-8_L5.0-W4.0-P1.27-LS6.2-BL,2,CJQ4435,C114076
Q3,SOT-363-6_L2.2-W1.3-P0.65-LS2.1-BL,1,currentmirror,C41375126
Q4,SOT-23,1,BSS84,C82079
Q5,SOIC-8_3.9x4.9mm_P1.27mm,1,AO4892,C357830
R1,R1206,1,11.3kohm,C44912
"R10, R52",R_0603,2,22kΩ,C31850
"R11, R15, R26, R60",R_0603,4,1MΩ,C22935
"R12, R13, R21, R30, R31, R35",R_0603,6,5.1kΩ,C23186
"R14, R16, R29, R39, R8, R9, RPROG3",R_0603,7,10kΩ,C25804
"R17, R24, R53",R_0603,3,2.2kΩ,C4190
R18,R_0603,1,6.8kΩ,C31850
R19,R_0603,1,2kΩ,C4211
R2,R0402,1,215kohm,C11489
R20,R_0603,1,2.2kΩ,C31850
R22,R_0603,1,240Ω,C23350
R25,R_0603,1,150Ω,C22808
R27,R0603,1,5.23kohm,C23068
R28,R0603,1,30.1kohm,C137745
"R3, R46",R_0603,2,3kΩ,C4211
"R32, RC0, RC1, RC2, RC3, R_SENSE1, R_SENSE2",R_0603,7,100Ω,C22775
R33,R_0603,1,10Ω,C22859
R34,R_0603,1,330kΩ,C23137
R36,R_0603,1,12kΩ,C22790
"R37, R44, R49, R77",R_0603,4,49.9kΩ,C23184
"R38, R45, R50, R6, R61, R76",R_0603,6,100kΩ,C25803
R4,R_0402,1,10Ω,C25077
"R40, R42, R47",R0805,3,511k,C17735
"R41, R43, R48",R0603,3,105k,C16840
R5,R0805,1,5.23k,C17739
R51,R0805,1,13.3k,C17446
R54,RES-ADJ-TH_3P-L7.3-W6.4-P5.00-R,1,RM065-204(200K),C5205025
R55,RES-ADJ-TH_3296W,1,3296W-1-504LF,C83694
"R56, R57, R58",R_0603,3,470Ω,C23179
R59,R_0603,1,110kΩ,C25805
R62,R0603,1,30.1k,C23000
"R63, R75",R0603,2,4.02k,C13211
R64,R_0402,1,1.5kΩ,C25867
"R65, RPROG1, RPROG2, RPROG5",R_0603,4,1kΩ,C21190
R66,R_0402,1,33kΩ,C25779
R7,R0603,1,32.4k,C13187
RIN1,R_0603,1,2Ω,C22977
RSENSE1,R0612,1,LTR18EZPFSR015,C510175
"R_AC1, R_AC2",R1206,2,10m,C105362
SW1,SW-SMD_L3.9-W3.0-P4.45,1,TS-1088R-02026,C455280
U1,TDFN-8_L2.0-W2.0-P0.50-BL-EP1.2,1,MAX17048G+T10,C2682616
"U10, U5",VQFN-24_L4.0-W4.0-P0.50-TL-EP2.8,2,BQ25606RGER,C374063
U11,CONN-TH_S2B-PH-K-S-GW,1,Battery Input,C157932
U12,VQFN-24_L5.5-W3.5-P0.50-BL-EP-2,1,BQ24170RGYR,C116999
"U13, U19, U20",SOT-23-6_L2.9-W1.6-P0.95-LS2.8-BL,3,TPS54302DDCR_C311983,C311983
"U14, U16",R0805,2,NTC10K/0805/F,C9900005726
U15,TSSOP-20_4.4x6.5mm_P0.65mm,1,BQ76920PW,
U17,DFN-10_L3.0-W3.0-P0.50-BL-EP2.5,1,HUSB238_002DD,C7471904
"U2, U3, U6",SOT-23-6_L2.9-W1.6-P0.95-LS2.8-BL,3,MT3608,
U21,QFN-20_L4.0-W4.0-P0.5-BL-EP,1,MCP73871,C511310
U22,IND-SMD_L4.5-W4.1_SRP4020TA,1,SRP4020TA-1R0M,C913245
U4,TSOT-23-6_L2.9-W1.6-P0.95-LS2.8-BR,1,TPL5110DDCT,C125830
U7,HDR-TH_20P-P2.54-V-M-R2-C10-S2.54,1,Z-21320110021001,C193453
U8,SSOP-16_L6.2-W5.3-P0.65-LS7.8-BL,1,MAX3232CDBR,C7257
U9,MSOP-10_L3.0-W3.0-P0.50-LS5.0-BL,1,ADS1115IDGSR,C37593
USBC1,USB-C_SMD-TYPE-C-31-M-12_1,1,TYPE-C-31-M-12,C165948

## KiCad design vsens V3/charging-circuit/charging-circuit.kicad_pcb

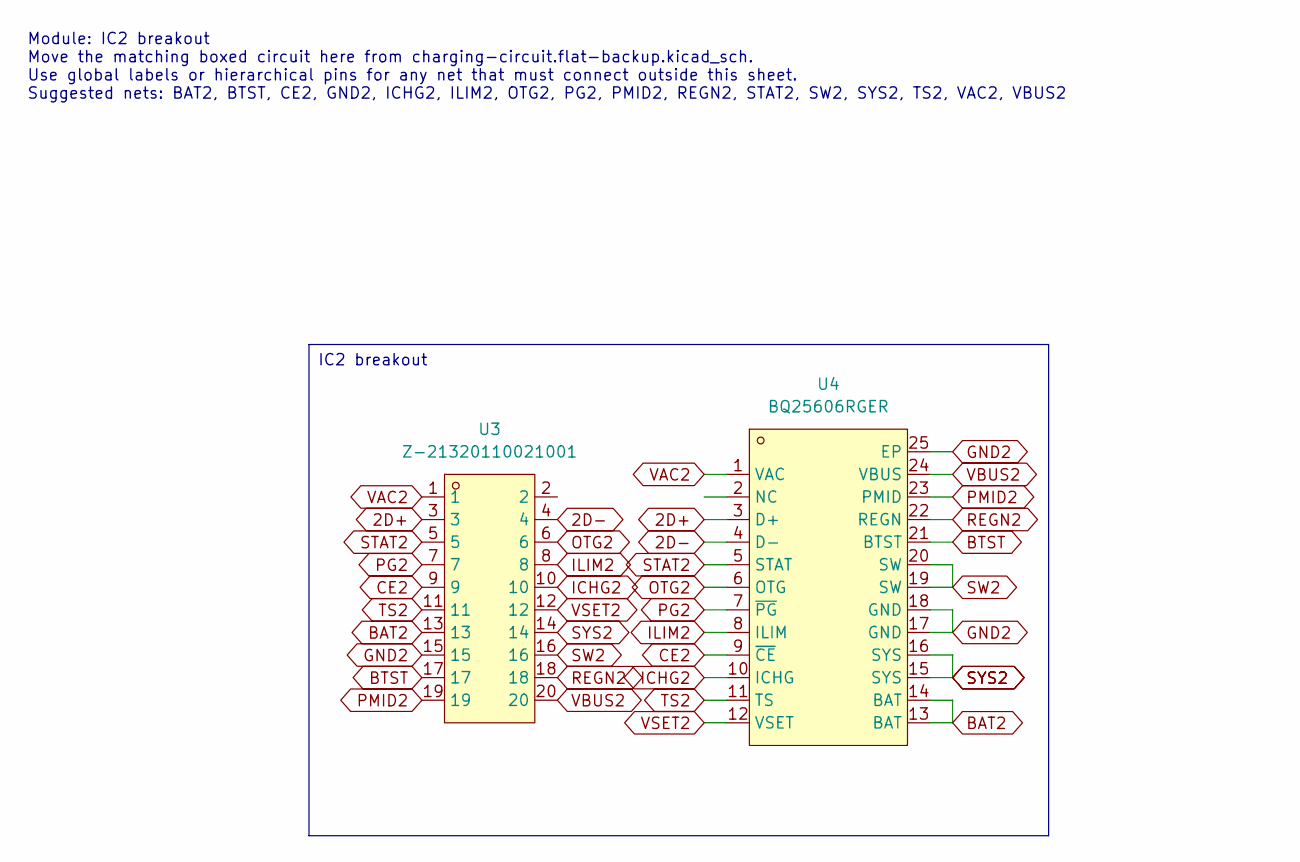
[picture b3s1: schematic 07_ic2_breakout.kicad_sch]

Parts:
U3: Z-21320110021001; HDR-TH_20P-P2.54-V-M-R2-C10-S2.54; LCSC Part C193453
U4: BQ25606RGER; VQFN-24_L4.0-W4.0-P0.50-TL-EP2.8; LCSC Part C374063

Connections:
2D+: U3.3, U4.3 (D+)
2D-: U3.4, U4.4 (D-)
BAT2: U3.13, U4.13 (BAT), U4.14 (BAT)
BTST: U3.17, U4.21 (BTST)
CE2: U3.9, U4.9 (~CE)
GND2: U3.15, U4.17 (GND), U4.18 (GND), U4.25 (EP)
ICHG2: U3.10, U4.10 (ICHG)
ILIM2: U3.8, U4.8 (ILIM)
OTG2: U3.6, U4.6 (OTG)
PG2: U3.7, U4.7 (~PG)
PMID2: U3.19, U4.23 (PMID)
REGN2: U3.18, U4.22 (REGN)
STAT2: U3.5, U4.5 (STAT)
SW2: U3.16, U4.19 (SW), U4.20 (SW)
SYS2: U3.14, U4.15 (SYS), U4.16 (SYS)
TS2: U3.11, U4.11 (TS)
VAC2: U3.1, U4.1 (VAC)
VBUS2: U3.20, U4.24 (VBUS)
VSET2: U3.12, U4.12 (VSET)

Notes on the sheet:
Module: IC2 breakout Move the matching boxed circuit here from charging-circuit.flat-backup.kicad_sch. Use global labels or hierarchical pins for any net that must connect outside this sheet. Suggested nets: BAT2, BTST, CE2, GND2, ICHG2, ILIM2, OTG2, PG2, PMID2, REGN2, STAT2, SW2, SYS2, TS2, VAC2, 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
IC2 breakout

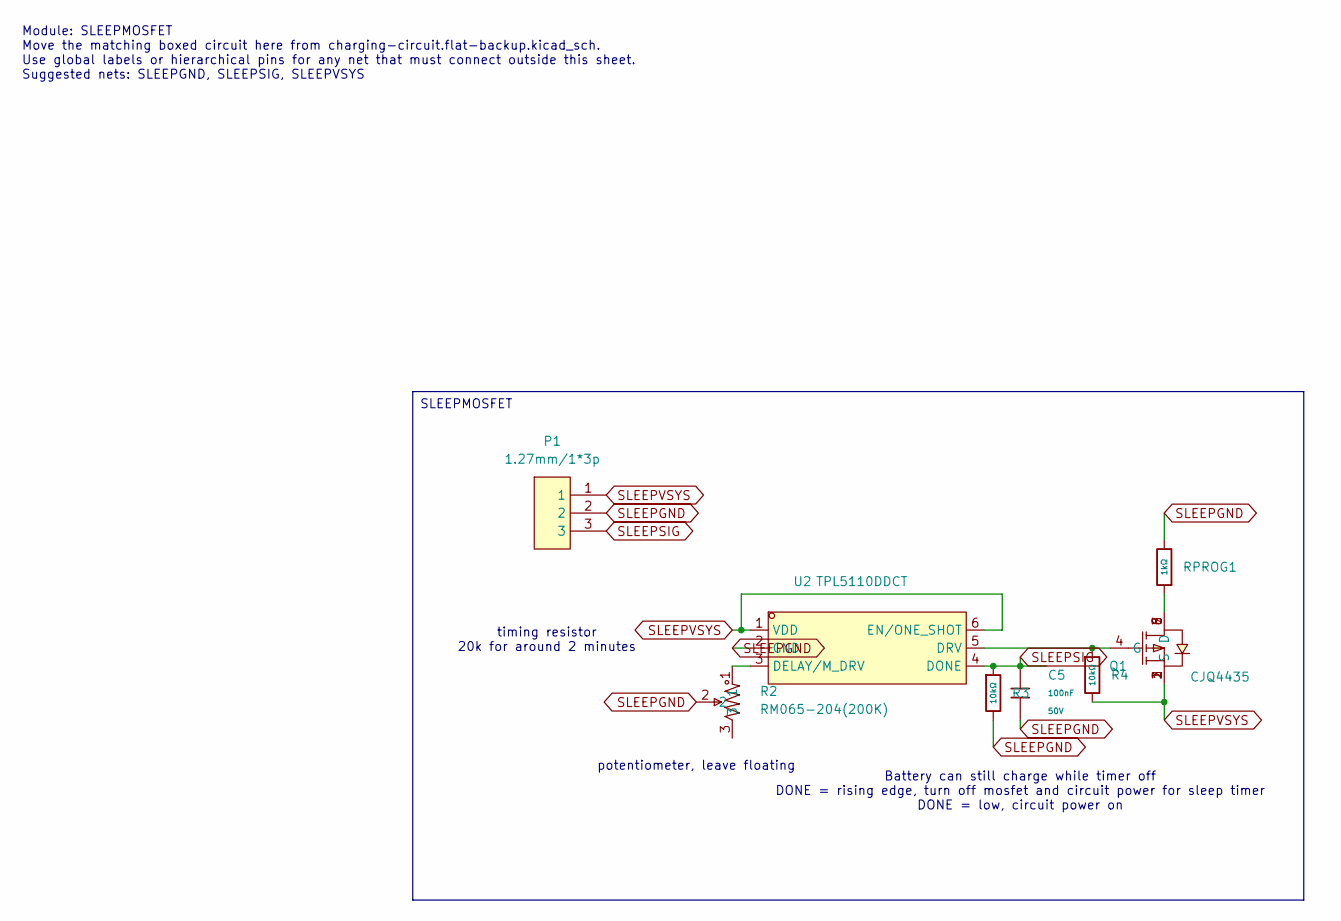
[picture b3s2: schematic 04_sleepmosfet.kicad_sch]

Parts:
C5: 100nF; C_0603; Voltage Rated 50V; Tolerance ±10%; Part CC0603KRX7R9BB104; LCSC C14663
P1: 1.27mm/1*3p; HDR-TH_3P-P1.27-V-M-1; LCSC Part C24980
Q1: CJQ4435; SOP-8_L5.0-W4.0-P1.27-LS6.2-BL; LCSC Part C114076
R2: RM065-204(200K); RES-ADJ-TH_3P-L7.3-W6.4-P5.00-R; LCSC Part C5205025
R3, R4: 10kΩ; R_0603; Overload Voltage (Max) 75V; Tolerance ±1%; Part 0603WAF1002T5E; LCSC C25804
RPROG1: 1kΩ; R_0603; Overload Voltage (Max) 75V; Tolerance ±1%; Part 0603WAF1001T5E; LCSC C21190
U2: TPL5110DDCT; TSOT-23-6_L2.9-W1.6-P0.95-LS2.8-BR; LCSC Part C125830

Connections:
unnamed: Q1.5 (D), Q1.6 (D), Q1.7 (D), Q1.8 (D), RPROG1.1
unnamed: Q1.4 (G), R4.1, U2.5 (DRV)
unnamed: R2.1, U2.3 (DELAY/M_DRV)
SLEEPGND: C5.2, P1.2, R2.2, R3.2, RPROG1.2, U2.2 (GND)
SLEEPSIG: C5.1, P1.3, R3.1, U2.4 (DONE)
SLEEPVSYS: P1.1, Q1.1 (S), Q1.2 (S), Q1.3 (S), R4.2, U2.1 (VDD), U2.6 (EN/ONE_SHOT)

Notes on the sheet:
Battery can still charge while timer off DONE = rising edge, turn off mosfet and circuit power for sleep timer DONE = low, circuit power on
potentiometer, leave floating
Module: SLEEPMOSFET Move the matching boxed circuit here from charging-circuit.flat-backup.kicad_sch. Use global labels or hierarchical pins for any net that must connect outside this sheet. Suggested nets: SLEEPGND, SLEEPSIG, SLEEPVSYS
timing resistor 20k for around 2 minutes
SLEEPMOSFET
